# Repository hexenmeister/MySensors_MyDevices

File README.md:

# MySensors_MyDevices
my own MySensors devices 

Etwas mehr dazu noch hier:<br>
http://www.s6z.de/cms/index.php/homeautomation/mysensors/63-up-bewegungsmelder-in-eigenbau<br>
http://www.s6z.de/cms/index.php/homeautomation/mysensors/66-mysensors-up-sensor-platine<br>
http://www.s6z.de/cms/index.php/homeautomation/mysensors/67-up-sensor-pir-temp-hum-lux-in-eigenbau<br>

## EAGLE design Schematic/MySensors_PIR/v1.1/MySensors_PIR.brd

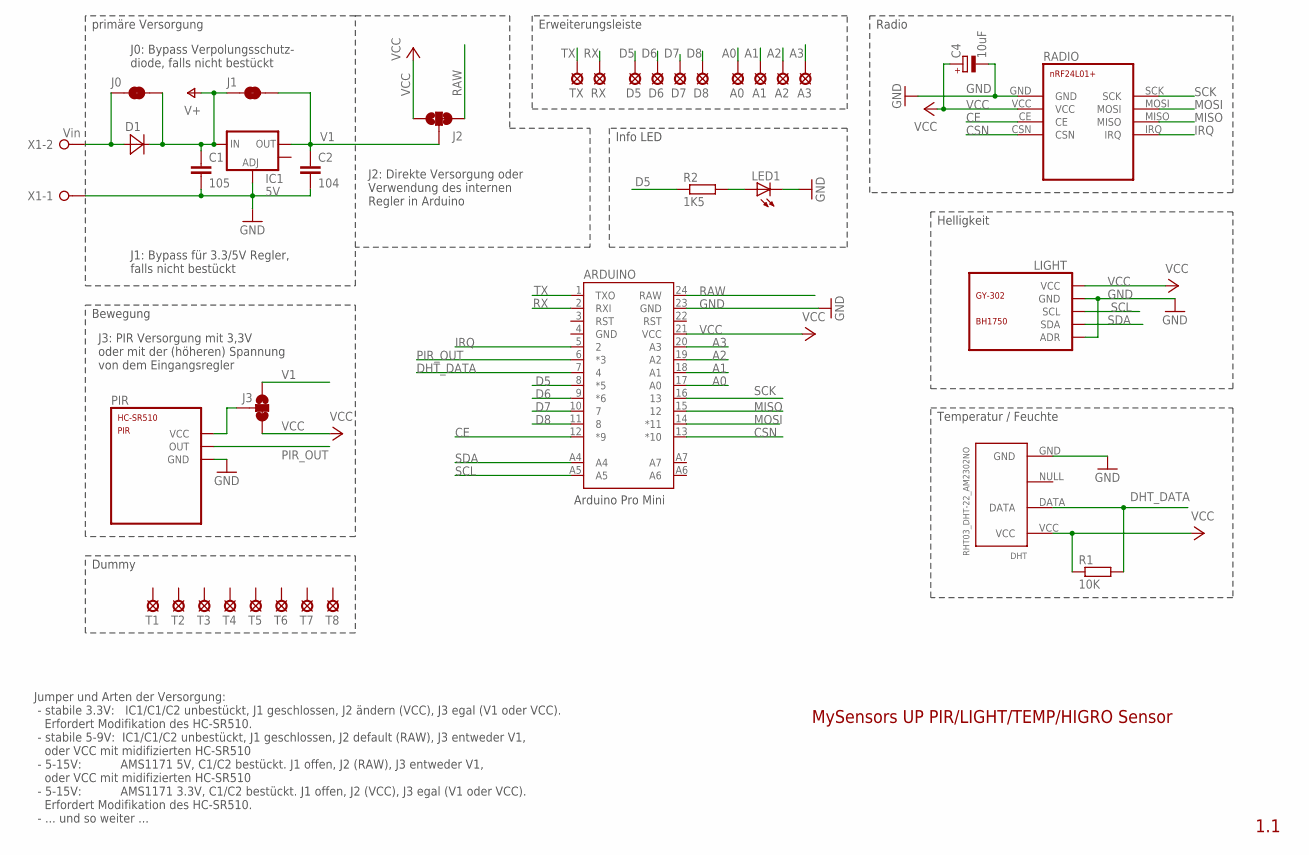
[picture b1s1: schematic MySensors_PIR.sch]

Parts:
A0, A1, A2, A3: LSP10
ARDUINO: ARDUINO_PRO_MININO; ARDUINO_PRO_MINI_O
C1: 105; C025-025X050
C2: 104; C025-025X050
C4: 10uF; E2,5-6E
D1: DIODE2.5U
D5, D6, D7, D8: LSP10
DHT: RHT03_DHT-22_AM2302NO; RHT03_DHT-22/RA_O
IC1: 5V; SOT223
J0, J1: JUMPER-PAD-2-NC_BY_TRACE; PAD-JUMPER-2-NC_BY_TRACE_YES_SILK
J2, J3: JUMPER-PAD-3-2OF3_NC_BY_TRACE_SMALL; PAD-JUMPER-3-2OF3_NC_BY_TRACE_YES_SILK_FULL_BOX
LED1: UNI_LED_3MM+SMD; LED3MM
LIGHT: GY-302
PIR: HC-SR501
R1: 10K; 0204V
R2: 1K5; 0204V
RADIO: NRF24L01+
RX: LSP10
T1, T2, T3, T4, T5, T6, T7, T8: LSP10
TX: LSP10
X1: Vin; W237-132

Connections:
A0: A0.1, ARDUINO.17 (A0)
A1: A1.1, ARDUINO.18 (A1)
A2: A2.1, ARDUINO.19 (A2)
A3: A3.1, ARDUINO.20 (A3)
CE: ARDUINO.12 (*9), RADIO.CE
CSN: ARDUINO.13 (*10), RADIO.CSN
D5: ARDUINO.8 (*5), D5.1, R2.1
D6: ARDUINO.9 (*6), D6.1
D7: ARDUINO.10 (7), D7.1
D8: ARDUINO.11 (8), D8.1
DHT_DATA: ARDUINO.7 (4), DHT.DATA, R1.2
GND: ARDUINO.23 (GND), C1.2, C2.2, C4.-, DHT.GND, IC1.1 (ADJ), LED1.K (C), LIGHT.ADR, LIGHT.GND, PIR.GND, RADIO.GND, X1.1
IRQ: ARDUINO.5 (2), RADIO.IRQ
MISO: ARDUINO.15 (12), RADIO.MISO
MOSI: ARDUINO.14 (*11), RADIO.MOSI
unnamed: LED1.A, R2.2
unnamed: D1.A, J0.1, X1.2
PIR_OUT: ARDUINO.6 (*3), PIR.OUT
PIR_VCC: J3.2, PIR.VCC
RAW: ARDUINO.24 (RAW), J2.3
RX: ARDUINO.2 (RXI), RX.1
SCK: ARDUINO.16 (13), RADIO.SCK
SCL: ARDUINO.A5, LIGHT.SCL
SDA: ARDUINO.A4, LIGHT.SDA
TX: ARDUINO.1 (TXO), TX.1
V1: C2.1, IC1.2 (OUT), J1.2, J2.2, J3.1
V+: C1.1, D1.K (C), IC1.3 (IN), J0.2, J1.1
VCC: ARDUINO.21 (VCC), C4.+, DHT.VCC, J2.1, J3.3, LIGHT.VCC, R1.1, RADIO.VCC

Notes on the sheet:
J0: Bypass Verpolungsschutz- diode, falls nicht bestückt
primäre Versorgung
Bewegung
J3: PIR Versorgung mit 3,3V oder mit der (höheren) Spannung von dem Eingangsregler
Temperatur / Feuchte
Erweiterungsleiste
Helligkeit
Radio
J2: Direkte Versorgung oder Verwendung des internen Regler in Arduino
Info LED
Arduino Pro Mini
J1: Bypass für 3.3/5V Regler, falls nicht bestückt
Jumper und Arten der Versorgung: - stabile 3.3V: IC1/C1/C2 unbestückt, J1 geschlossen, J2 ändern (VCC), J3 egal (V1 oder VCC). Erfordert Modifikation des HC-SR510. - stabile 5-9V: IC1/C1/C2 unbestückt, J1 geschlossen, J2 default (RAW), J3 entweder V1, oder VCC mit midifizierten HC-SR510 - 5-15V: AM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
1.1
MySensors UP PIR/LIGHT/TEMP/HIGRO Sensor
Dummy

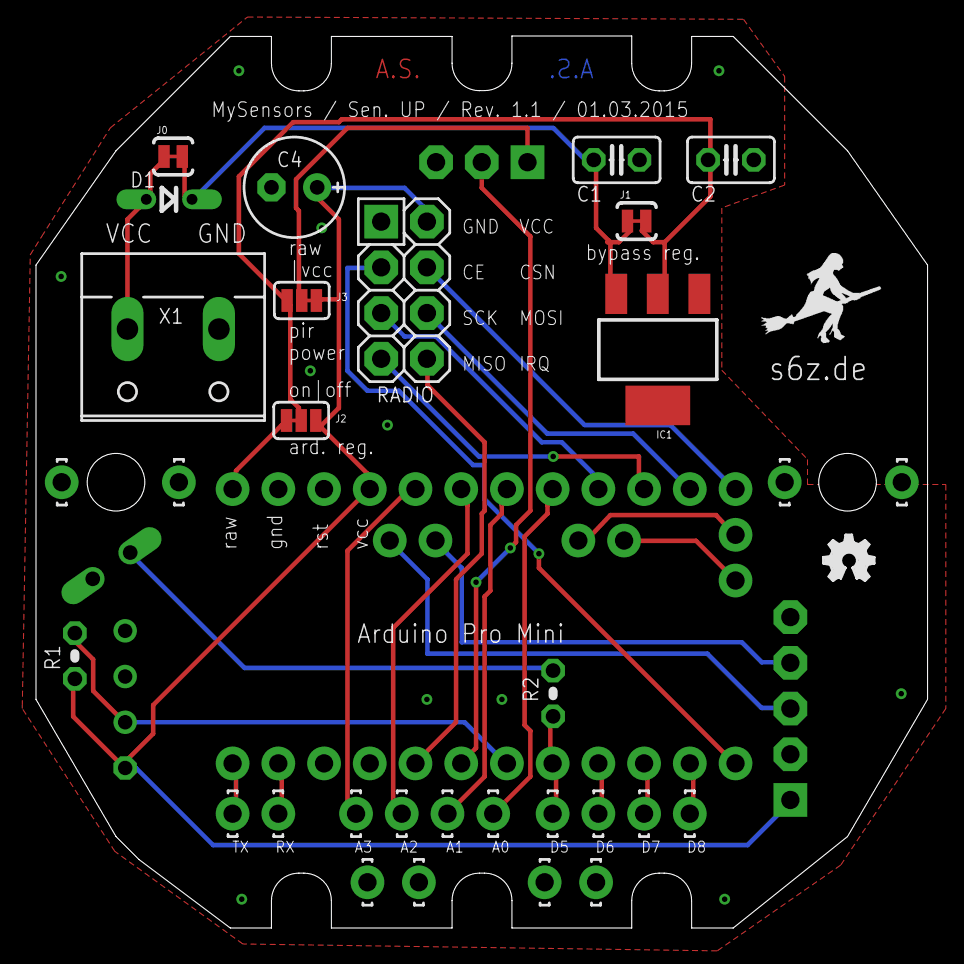
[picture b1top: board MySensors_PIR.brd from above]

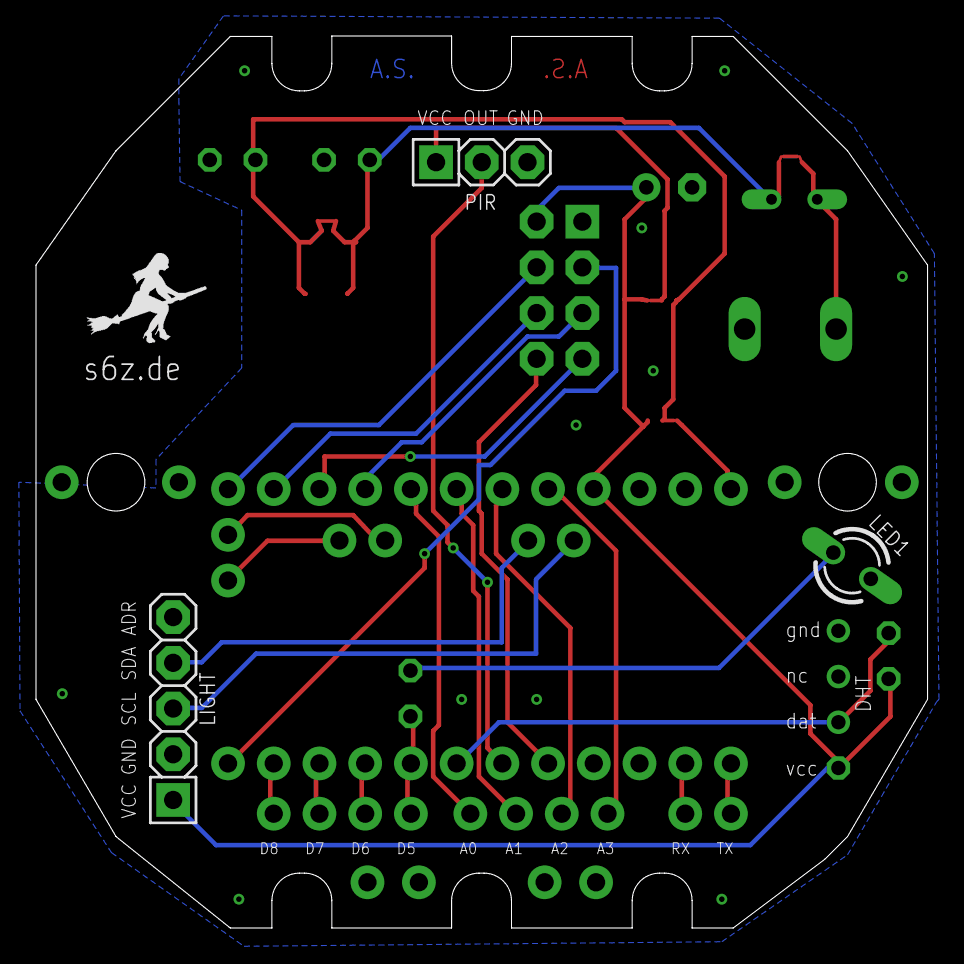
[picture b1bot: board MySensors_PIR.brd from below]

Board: 2 copper layers, 49.5 x 49.6 mm, 37 parts (4 on the bottom side), 28 nets.

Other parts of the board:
U$2: OSHW_FILLX100_NOTEXT

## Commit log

2015-02-16 initial
2015-03-03 little changes
2015-03-03 dummy pins
2015-03-19 initial / std. sketch with aktivated WatchdogTimer (2s)
2015-04-13 use watchdog
2015-04-13 obsolete
2015-09-08 ESP8266 WLAN Gateway : Initial version
2015-09-27 fix: sleep, interrupt, pullup activation,
2015-09-27 fix: sleep, interrupt
2015-10-11 quick fix: line endings for FHEM
2015-10-25 Lux: asyncron lesen etwas Bereinigung
2015-10-26 alte LED-Methoden ausgebaut
2015-11-20 feature: static ip config
2015-11-21 fix: static ip
2016-02-12 Update MyEsp8266Gateway.ino
    Line 180
    WiFi.mode (WIFI_STA); // turn off AP mode
2016-02-13 Debug

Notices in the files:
parts and their libraries:
SparkFun-Passives: Licensing: Creative Commons ShareAlike 4.0 International - https://creativecommons.org/licenses/by-sa/4.0
